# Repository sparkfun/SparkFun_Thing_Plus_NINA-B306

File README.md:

# SparkFun Thing Plus - NINA-B306

[SparkFun Thing Plus - NINA-B306 (WRL-20854)](https://www.sparkfun.com/products/20854)

The SparkFun Thing Plus - NINA-B306 offers a unique combination development platform in the Thing Plus form factor featuring the NINA-B306 from u-blox<sup>&trade;</sup>, the ISM330DHCX 6 DoF IMU from STMicroelectronics<sup>&trade;</sup> and the BME280 atmospheric sensor from Bosch Sensortec<sup>&trade;</sup>.

The NINA-B306 is a combination Bluetooth<sup>&trade;</sup> 5 module with an Arm<sup>&reg;</sup> Cortex<sup>&reg;</sup>-M4 processor. The NINA-B306 features an integrated PCB antenna removing the need for any external antenna. It includes 1 MB Flash and 250 kB RAM.

The BME280 combined humidity and pressure sensor measures barometric pressure, humidity and ambient temperature in a small package. The sensor measures pressure from 300 to 1100 hPa and has a full temperature accuracy range from 0 to 65&deg;C. The sensor communicates with the NINA-B306 over I<sup>2</sup>C.

The ISM330DHCX 6DoF IMU is a high-performance 3D digital accelerometer and 3D digital gyroscope tailored for Industry 4.0. The IMU has full scale user selectable acceleration ranges of &plusmn;2/&plusmn;4/&plusmn;8/&plusmn;16g and wide angular rate ranges of &plusmn;125/&plusmn;250/&plusmn;500/&plusmn;1000/&plusmn;2000/&plusmn;4000dps. The ISM330DHCX has embedded features including Machine Learning Core<sup><a href="#IMU_Mode">1</a></b></sup>, programmable FSM, FIFO, sensor hub, event decoding, and interrupts.

## Repository Contents

- **/Documentation** - Data sheets, additional product information
- **/Firmware** - Example code
- **/Hardware** - Eagle design files (.brd, .sch)
- **/Production** - Production panel files (.brd)

## Documentation

- **[BME280 Library](https://github.com/sparkfun/SparkFun_BME280_Arduino_Library)** - Arduino library for the BME280.
- **[ISM330DHCX Library](https://github.com/sparkfun/SparkFun_6DoF_ISM330DHCX_Arduino_Library)** - Arduino library for the ISM330DHCX.
- **[MAX17048 Library](https://github.com/sparkfun/SparkFun_MAX1704x_Fuel_Gauge_Arduino_Library)** - Arduino library for the MAX1704X.
- **[Hookup Guide](https://learn.sparkfun.com/tutorials/sparkfun-thing-plus---nina-b306-hookup-guide)** - Basic hookup guide for the SparkFun Thing Plus - NINA-B306.

## Product Versions

- [WRL-20854](https://www.sparkfun.com/products/20854) - Initial release of the SparkFun Thing Plus - NINA-B306.

## License Information

This product is _**open source**_!

Please review the LICENSE.md file for license information.

If you have any questions or concerns on licensing, please contact technical support on our [SparkFun forums](https://forum.sparkfun.com/viewforum.php?f=152).

Distributed as-is; no warranty is given.

- Your friends at SparkFun.

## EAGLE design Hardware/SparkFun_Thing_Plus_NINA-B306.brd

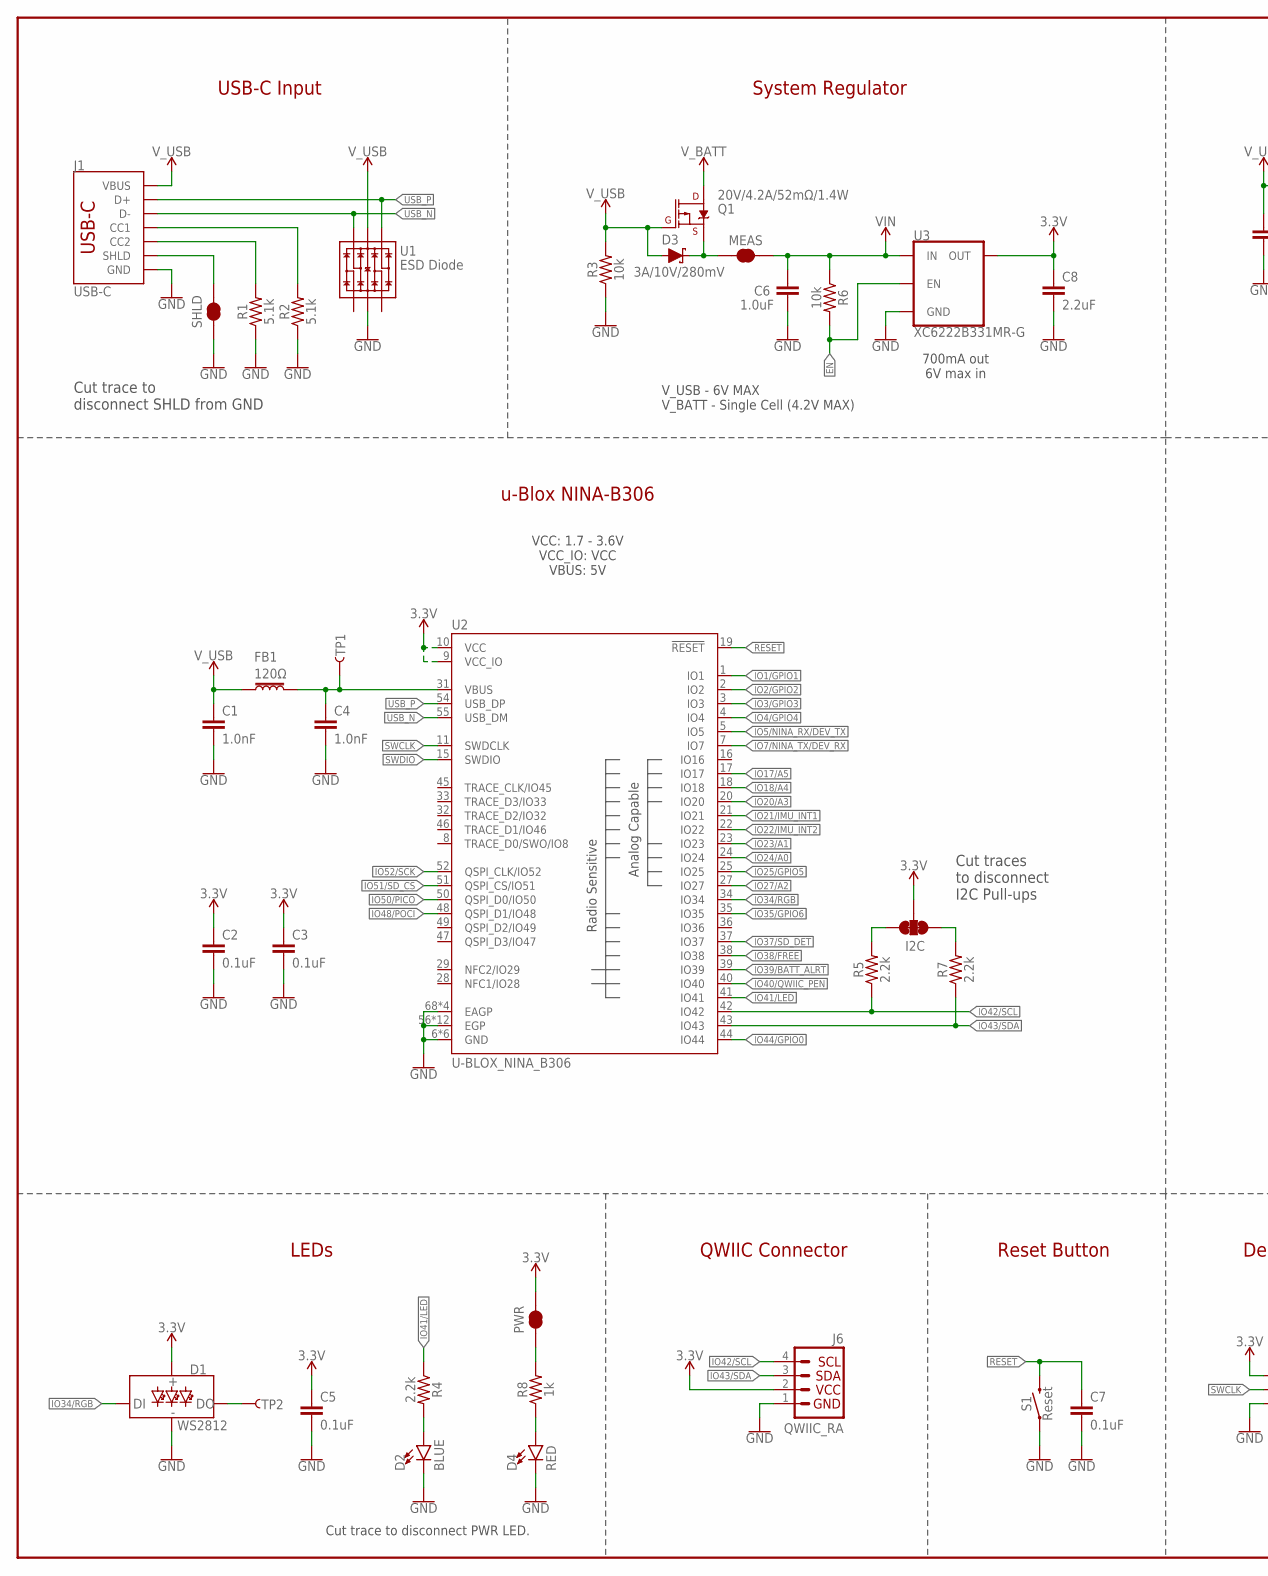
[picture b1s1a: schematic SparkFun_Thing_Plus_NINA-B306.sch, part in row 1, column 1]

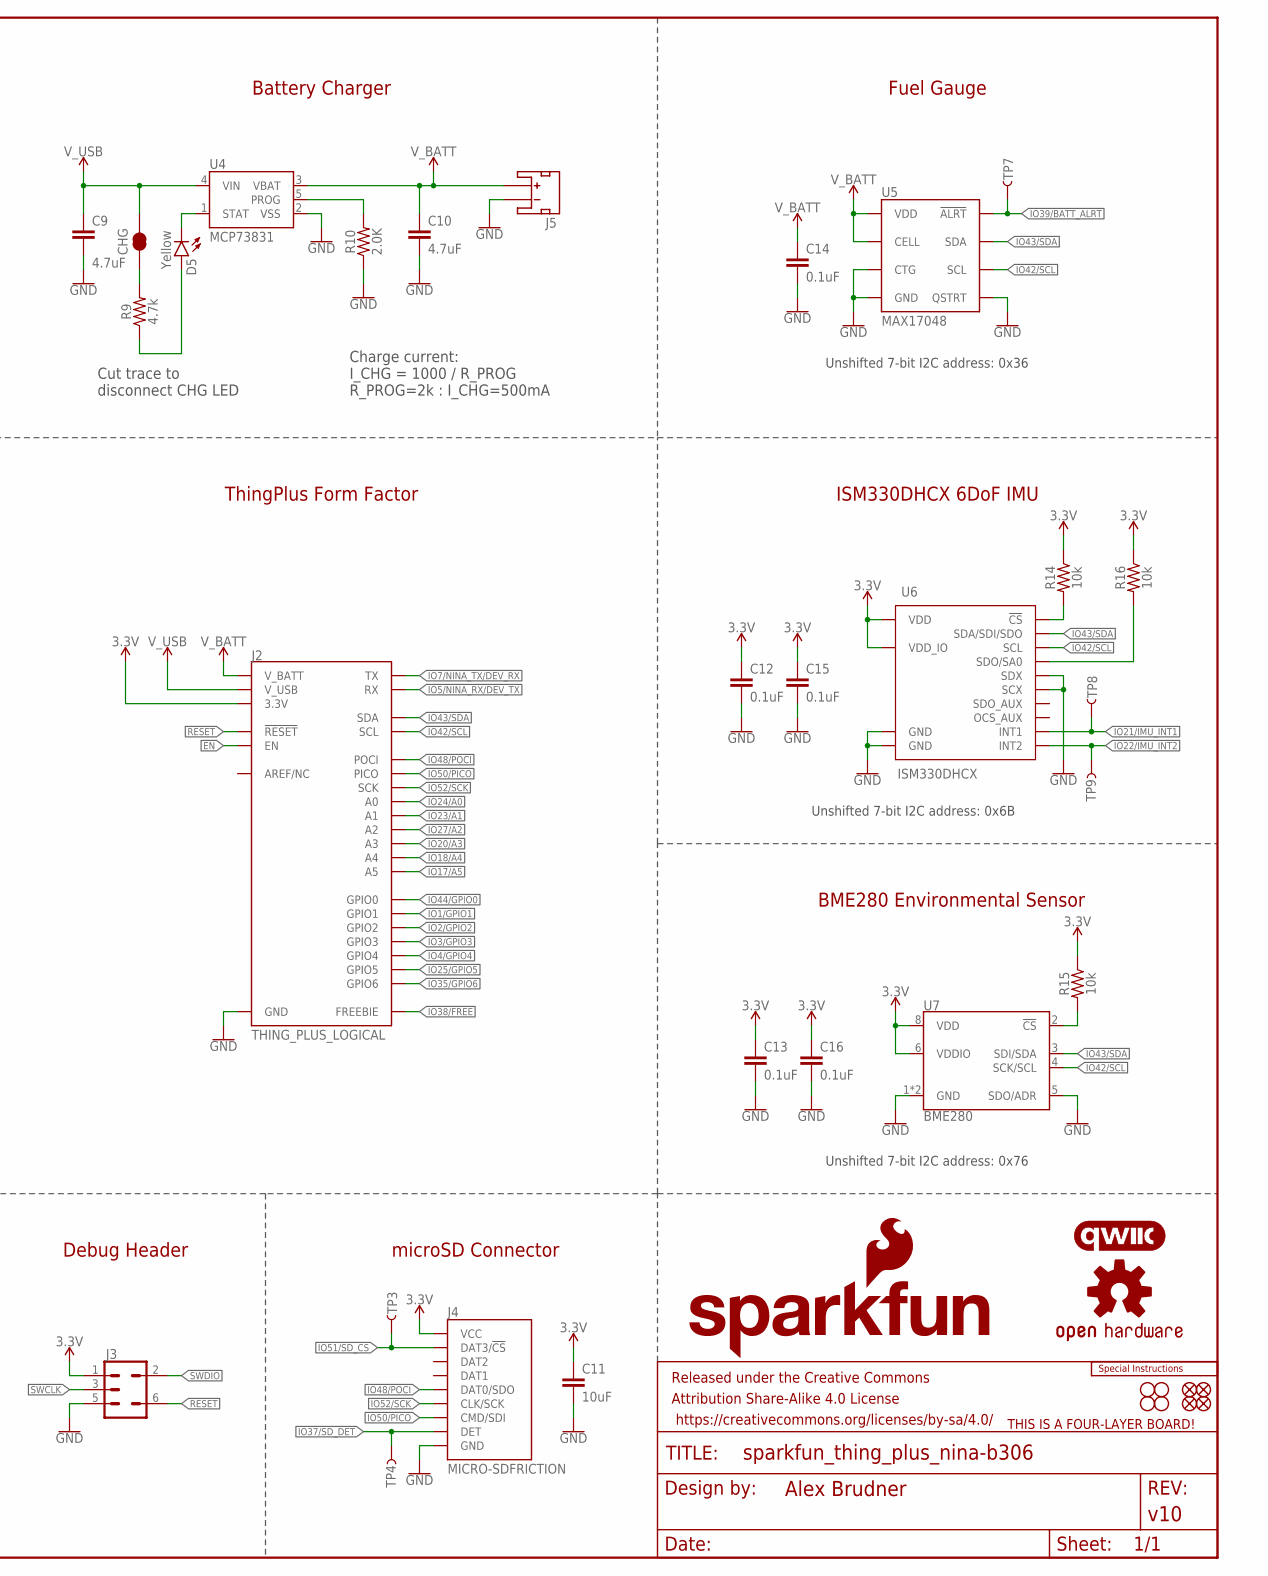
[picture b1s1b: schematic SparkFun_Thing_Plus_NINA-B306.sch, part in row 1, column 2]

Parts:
C1, C4: 1.0nF; 0402-TIGHT
C2, C3, C5, C7, C12, C13, C14, C15, C16: 0.1uF; 0402-TIGHT
C6: 1.0uF; 0402-TIGHT
C8: 2.2uF; 0402-TIGHT
C9, C10: 4.7uF; 0402-TIGHT
C11: 10uF; 0402-TIGHT
CHG: JUMPER-SMT_2_NC_TRACE_SILK; SMT-JUMPER_2_NC_TRACE_SILK
D1: WS2812; WS2812-2020
D2: BLUE; LED-0603
D3: 3A/10V/280mV; SOD-323
D4: RED; LED-0603
D5: Yellow; LED-0603
FB1: 120Ω; 0402
FD1, FD2, FD3, FD4: FIDUCIALUFIDUCIAL; FIDUCIAL-MICRO
FRAME1: FRAME-LEDGER; CREATIVE_COMMONS
H1, H2, H3, H4: STAND-OFFTIGHT; STAND-OFF-TIGHT
I2C: JUMPER-SMT_3_2-NC_TRACE_SILK; SMT-JUMPER_3_2-NC_TRACE_SILK
J1: USB-C; USB-C-16P-4LAYER-ISOLATED
J2: THING_PLUS_LOGICAL; THING_PLUS
J3: CONN_03X2_NO4; PAD_05_03X2_TP_NO4
J4: MICRO-SDFRICTION; MICROSD_TINY
J5: JST_2MM_MALE; JST-2-SMD
J6: QWIIC_RA; JST04_1MM_RA
LOGO1: SFE_LOGO_NAME_FLAME.1_INCH; SFE_LOGO_NAME_FLAME_.1
LOGO2: FOUR_LAYER_WARNING
LOGO3: SPECIAL_INSTRUCTIONS-ORDERING; ORDERING_INSTRUCTIONS
LOGO4: QWIIC_LOGO_4MM; QWIIC_4MM
LOGO5: OSHW-LOGOMINI; OSHW-LOGO-MINI
MEAS: JUMPER-COMBO_2_NC_TRACE; COMBO-JUMPER_2_NC_TRACE
PWR: JUMPER-SMT_2_NC_TRACE_SILK; SMT-JUMPER_2_NC_TRACE_SILK
Q1: 20V/4.2A/52mΩ/1.4W; SOT23-3
R1, R2: 5.1k; 0402-TIGHT
R3, R6, R14, R15, R16: 10k; 0402-TIGHT
R4, R5, R7: 2.2k; 0402-TIGHT
R8: 1k; 0402-TIGHT
R9: 4.7k; 0402-TIGHT
R10: 2.0K; 0402-TIGHT
S1: Reset; TACTILE_SWITCH_SMD_4.6X2.8MM
SHLD: JUMPER-SMT_2_NC_TRACE_SILK; SMT-JUMPER_2_NC_TRACE_SILK
TP1, TP2, TP3, TP4, TP7, TP8, TP9: TEST-POINT3X5; PAD.03X.05
U1: ESD Diode; SOT-23-6
U2: U-BLOX_NINA_B306; NINA_B306
U3: XC6222B331MR-G; SOT23-5
U4: MCP73831; SOT23-5
U5: MAX17048; DFN-8
U6: ISM330DHCX; LGA-14L
U7: BME280; LGA-8-2.5X2.5

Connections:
3.3V: C2.1, C3.1, C5.1, C8.1, C11.1, C12.1, C13.1, C15.1, C16.1, D1.VCC, I2C.2, J2.27 (3.3V), J3.1, J4.4 (VCC), J6.2, PWR.2, R14.1, R15.1, R16.1, U2.9 (VCC_IO), U2.10 (VCC), U3.5 (OUT), U6.P5 (VDD_IO), U6.P8 (VDD), U7.6 (VDDIO), U7.8 (VDD)
!RESET!: C7.1, J2.28 (!RESET), J3.6, S1.3 (2), S1.4 (2), U2.19 (!RESET!)
EN: J2.11 (EN), R6.2, U3.3 (EN)
GND: C1.2, C2.2, C3.2, C4.2, C5.2, C6.2, C7.2, C8.2, C9.2, C10.2, C11.2, C12.2, C13.2, C14.2, C15.2, C16.2, D1.GND, D2.C, D4.C, J1.GND, J1.GND2 (GND), J2.25 (GND), J3.5, J4.6 (GND), J4.GND1 (GND), J4.GND2 (GND), J4.GND3 (GND), J4.GND4 (GND), J4.GND5 (GND), J4.GND6 (GND), J5.1 (-), J6.1, R1.1, R2.1, R3.1, R10.1, S1.1, S1.2 (1), SHLD.1, U1.2 (VSS), U2.6 (GND), U2.12 (GND), U2.14 (GND), U2.26 (GND), U2.30 (GND), U2.53 (GND), U2.56 (EGP), U2.57 (EGP), U2.58 (EGP), U2.59 (EGP), U2.60 (EGP), U2.61 (EGP), U2.62 (EGP), U2.63 (EGP), U2.64 (EGP), U2.65 (EGP), U2.66 (EGP), U2.67 (EGP), U2.68 (EAGP), U2.69 (EAGP), U2.70 (EAGP), U2.71 (EAGP), U3.2 (GND), U4.2 (VSS), U5.1 (CTG), U5.4 (GND), U5.6 (QSTRT), U5.9 (GND), U6.P2 (SDX), U6.P3 (SCX), U6.P6 (GND), U6.P7 (GND), U7.1 (GND), U7.5 (SDO/ADR), U7.7 (GND)
IO1/GPIO1: J2.8 (GPIO1), U2.1 (IO1)
IO2/GPIO2: J2.7 (GPIO2), U2.2 (IO2)
IO3/GPIO3: J2.6 (GPIO3), U2.3 (IO3)
IO4/GPIO4: J2.5 (GPIO4), U2.4 (IO4)
IO5/NINA_RX/DEV_TX: J2.15 (RX), U2.5 (IO5)
IO7/NINA_TX/DEV_RX: J2.14 (TX), U2.7 (IO7)
IO17/A5: J2.19 (A5), U2.17 (IO17)
IO18/A4: J2.20 (A4), U2.18 (IO18)
IO20/A3: J2.21 (A3), U2.20 (IO20)
IO21/IMU_INT1: TP8.1, U2.21 (IO21), U6.P4 (INT1)
IO22/IMU_INT2: TP9.1, U2.22 (IO22), U6.P9 (INT2)
IO23/A1: J2.23 (A1), U2.23 (IO23)
IO24/A0: J2.24 (A0), U2.24 (IO24)
IO25/GPIO5: J2.4 (GPIO5), U2.25 (IO25)
IO27/A2: J2.22 (A2), U2.27 (IO27)
IO34/RGB: D1.DI, U2.34 (IO34)
IO35/GPIO6: J2.3 (GPIO6), U2.35 (IO35)
IO37/SD_DET: J4.9 (DET), TP4.1, U2.37 (IO37)
IO38/FREE: J2.13 (FREEBIE), U2.38 (IO38)
IO39/!BATT_ALRT!: TP7.1, U2.39 (IO39), U5.5 (!ALRT)
IO40/QWIIC_!PEN!: U2.40 (IO40)
IO41/LED: R4.1, U2.41 (IO41)
IO42/SCL: J2.2 (SCL), J6.4, R5.1, U2.42 (IO42), U5.7 (SCL), U6.P13 (SCL), U7.4 (SCK/SCL)
IO43/SDA: J2.1 (SDA), J6.3, R7.1, U2.43 (IO43), U5.8 (SDA), U6.P14 (SDA/SDI/SDO), U7.3 (SDI/SDA)
IO44/GPIO0: J2.9 (GPIO0), U2.44 (IO44)
IO48/POCI: J2.16 (POCI), J4.7 (DAT0/SDO), U2.48 (QSPI_D1/IO48)
IO50/PICO: J2.17 (PICO), J4.3 (CMD/SDI), U2.50 (QSPI_D0/IO50)
IO51/SD_!CS!: J4.2 (DAT3/!CS!), TP3.1, U2.51 (QSPI_CS/IO51)
IO52/SCK: J2.18 (SCK), J4.5 (CLK/SCK), U2.52 (QSPI_CLK/IO52)
unnamed: J1.B5 (CC2), R1.2
unnamed: J1.A5 (CC1), R2.2
unnamed: D5.A, R9.1
unnamed: D5.C, U4.1 (STAT)
unnamed: R10.2, U4.5 (PROG)
unnamed: CHG.1, R9.2
unnamed: D4.A, R8.1
unnamed: PWR.1, R8.2
unnamed: D3.C, MEAS.1, MEAS.3 (1), Q1.2 (S)
unnamed: D1.DO, TP2.1
unnamed: R15.2, U7.2 (!CS)
unnamed: D2.A, R4.2
unnamed: R14.2, U6.P12 (!CS!)
unnamed: R16.2, U6.P1 (SDO/SA0)
unnamed: C4.1, FB1.2, TP1.1, U2.31 (VBUS)
SCL_PU_PWR: I2C.3, R5.2
SDA_PU_PWR: I2C.1, R7.2
SHLD: J1.SHLD1 (SHLD), J1.SHLD2 (SHLD), J1.SHLD3 (SHLD), J1.SHLD4 (SHLD), J1.SHLD5 (SHLD), J1.SHLD6 (SHLD), J1.SHLD7 (SHLD), J1.SHLD8 (SHLD), SHLD.2
SWCLK: J3.3, U2.11 (SWDCLK)
SWDIO: J3.2, U2.15 (SWDIO)
USB_N: J1.A7 (D-), J1.B7 (D-), U1.6 (IO4), U2.55 (USB_DM)
USB_P: J1.A6 (D+), J1.B6 (D+), U1.4 (IO3), U2.54 (USB_DP)
VIN: C6.1, MEAS.2, MEAS.4 (2), R6.1, U3.1 (IN)
V_BATT: C10.1, C14.1, J2.12 (V_BATT), J5.2 (+), Q1.3 (D), U4.3 (VBAT), U5.2 (CELL), U5.3 (VDD)
V_USB: C1.1, C9.1, CHG.2, D3.A, FB1.1, J1.VBUS1 (VBUS), J1.VBUS2 (VBUS), J2.10 (V_USB), Q1.1 (G), R3.2, U1.5 (VCC), U4.4 (VIN)

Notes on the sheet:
Battery Charger
Cut trace to disconnect CHG LED
Charge current: I_CHG = 1000 / R_PROG R_PROG=2k : I_CHG=500mA
System Regulator
700mA out 6V max in
V_USB - 6V MAX V_BATT - Single Cell (4.2V MAX)
USB-C Input
Fuel Gauge
Unshifted 7-bit I2C address: 0x36
Cut trace to disconnect SHLD from GND
microSD Connector
Debug Header
LEDs
Reset Button
u-Blox NINA-B306
ThingPlus Form Factor
QWIIC Connector
Cut traces to disconnect I2C Pull-ups
BME280 Environmental Sensor
Unshifted 7-bit I2C address: 0x76
Unshifted 7-bit I2C address: 0x6B
ISM330DHCX 6DoF IMU
VCC: 1.7 - 3.6V VCC_IO: VCC VBUS: 5V
Cut trace to disconnect PWR LED.

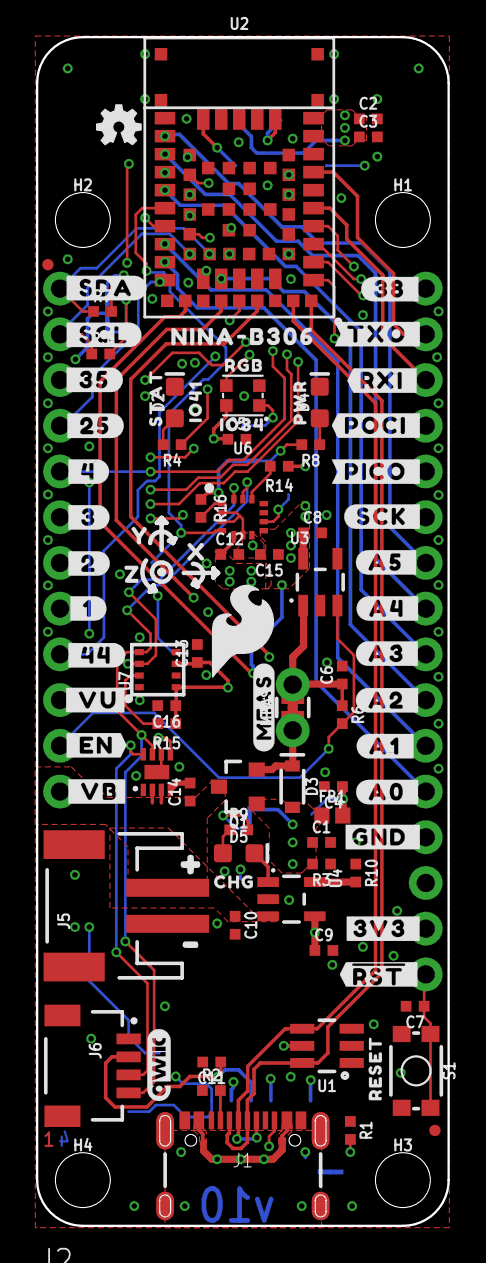
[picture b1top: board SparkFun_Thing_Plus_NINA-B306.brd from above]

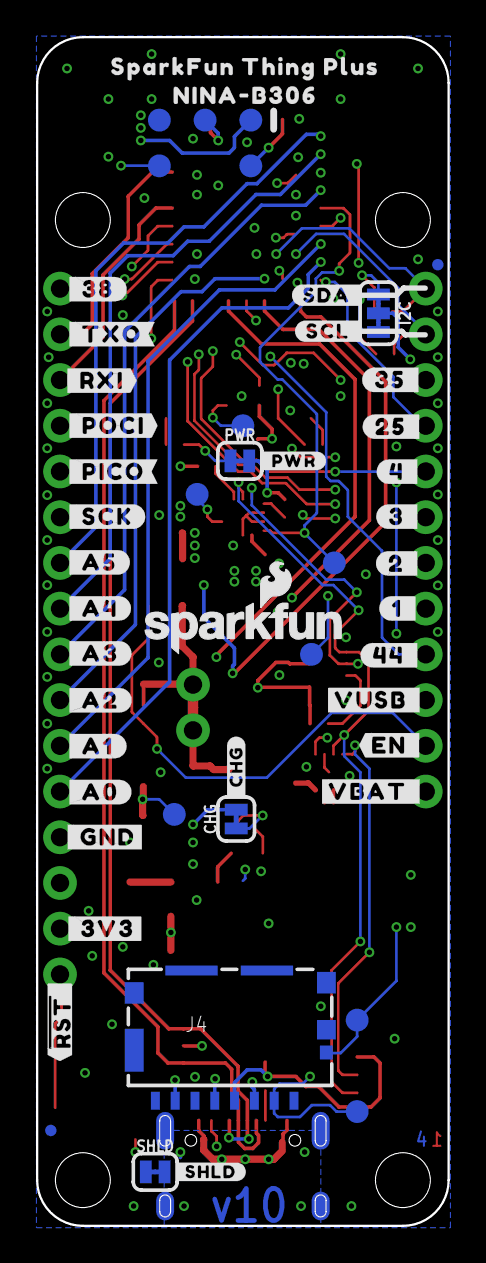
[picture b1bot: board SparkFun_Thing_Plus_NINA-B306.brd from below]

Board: 4 copper layers, 22.9 x 66.0 mm, 151 parts (49 on the bottom side), 57 nets.

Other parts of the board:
U$1: SFE_LOGO_FLAME_STOP_.1
U$2: SFE_LOGO_FLAME_.2
U$3: #_VU#0
U$4: #_EN#47
U$5: #3V3_#0
U$6: #_44#49
U$7: #_1#49
U$8: #_2#49
U$9: #_3#49
U$10: #_4#49
U$11: #_25#49
U$12: #_35#0
U$13: #_SCL#49
U$14: RESET0
U$16: #GND_#53
U$17: #A0_#54
U$18: #A1_#54
U$19: #A2_#54
U$20: #A3_#54
U$21: #A4_#54
U$22: #A5_#54
U$23: #SCK_#54
U$24: #PICO_#60
U$25: #POCI_#61
U$26: #TXO_#57
U$27: #RXI_#59
U$28: #38_#60
U$29: #_SDA#68
U$30: #_CHG#30707
U$31: #_3V3#0
U$32: #_GND#70
U$33: #_A0#71
U$34: #_A1#71
U$35: #_A2#71
U$36: #_A3#71
U$37: #_A4#71
U$38: #_A5#71
U$39: #_SCK#71
U$40: #_PICO#72
U$41: #_POCI#73
U$42: #_TXO#74
U$43: #_RXI#75
U$44: #_38#76
U$45: #35_#0
U$46: #25_#79
U$47: #4_#79
U$48: #3_#79
U$49: #2_#79
U$50: #1_#79
U$51: #44_#79
U$52: #VBAT_#0
U$53: #EN_#80
U$54, U$74: ##RST#_#0
U$55: #SDA_#82
U$56: #SCL_#85
U$57: #_PWR#90
U$58: #VUSB_#0
U$59: #_SHLD#93
U$60: SPARKFUN_THING_PLUS96
U$61: NINA#B30697
U$62: #MEAS#30701
U$63: #_VB#0
U$64: RGB30710
U$65: STAT30711
U$66: PWR30712
U$67: NINA#B30630713
U$68: X2114
U$69: Y2115
U$70: Z2116
U$71: IO414130630715
U$72: IO34414130630716
U$73: CHG0
U$75: #3
U$76: #4

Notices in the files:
parts and their libraries:
SparkFun-Aesthetics: Licensing: Creative Commons ShareAlike 4.0 International - https://creativecommons.org/licenses/by-sa/4.0
SparkFun-Aesthetics: Released under the Creative Commons Attribution Share-Alike 4.0 License
SparkFun-Aesthetics: https://creativecommons.org/licenses/by-sa/4.0
